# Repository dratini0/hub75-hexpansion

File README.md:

# HUB75 hexpansion

As of yet untested

Drives an LED wall panel by a single SPI peripheral.
A single 74HC595 drives the line select lines, this is inserted before the panel.
Then, the serial stream goes through the shift registers in the panel, and it is fed back into the input of the panel from the daisy chain output.
This means that a panel that normally needs a 6-way parallel drive can now be driven with just a single SPI line.
The OE pin is broken out to the high speed IO for a good measure.

The order of the chain is as follows:
1. Shift register
2. R1
3. G1
4. B1
5. R2
6. G2
7. B2

## Acknowledgements

Uses the [hexpansion template from EMF](https://github.com/emfcamp/badge-2024-hardware/tree/main/hexpansion)

I have taken the idea of chaining an LED wall panel with itself from some Youtube video that I have seen years and years ago, and I can no longer locate.

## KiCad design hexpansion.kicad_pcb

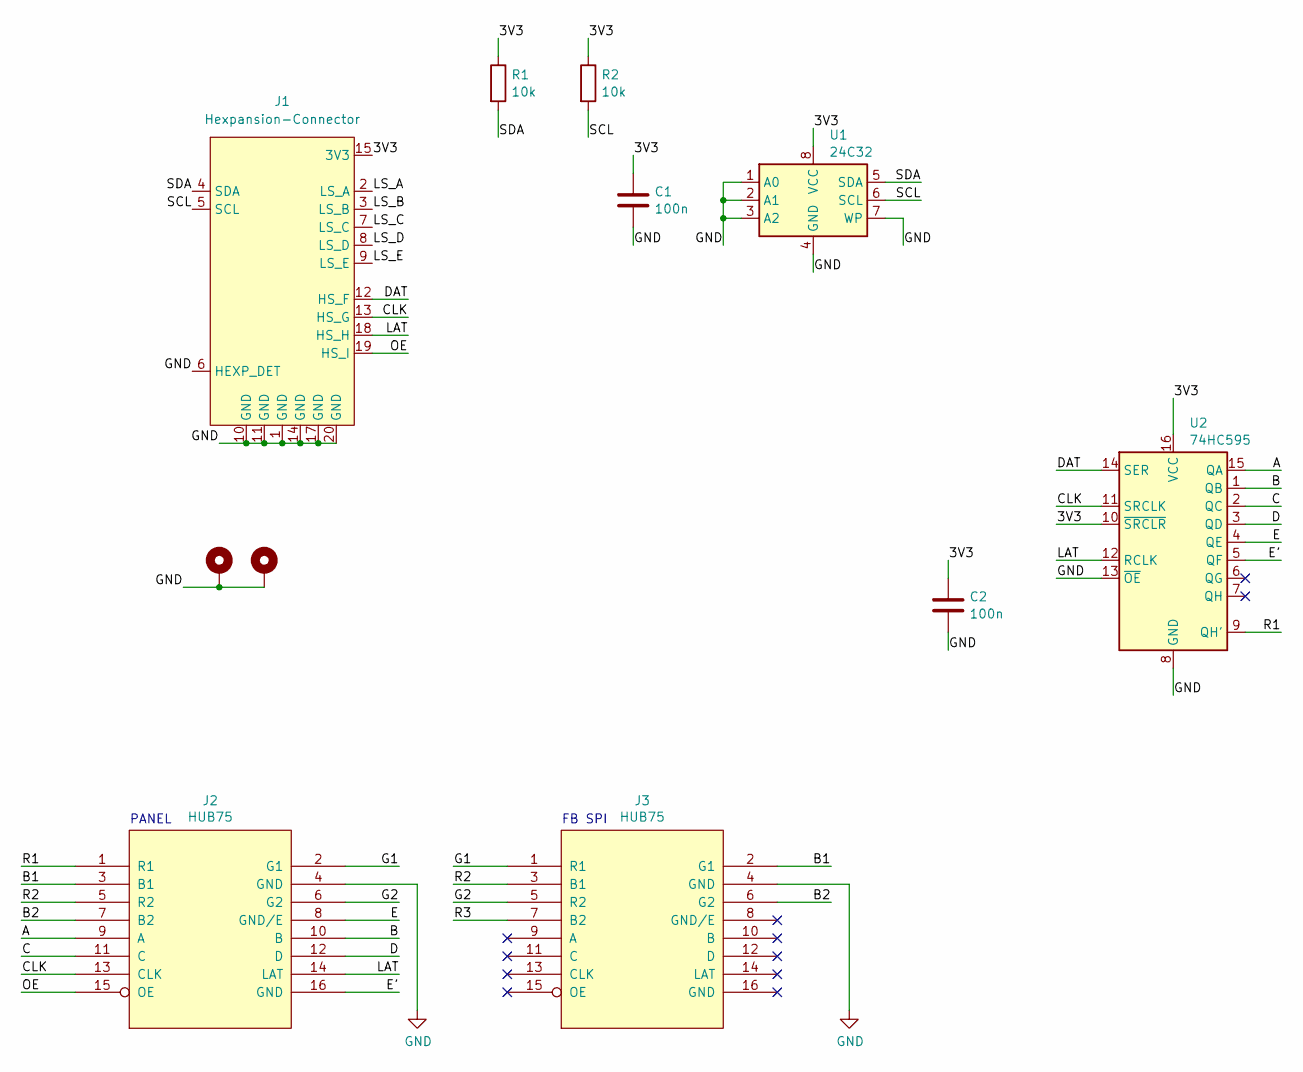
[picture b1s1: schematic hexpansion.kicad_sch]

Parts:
C1, C2: 100n; C_0805_2012Metric_Pad1.18x1.45mm_HandSolder
H1, H2: MountingHole_Pad; MountingHole_2.2mm_M2_Pad_Via
J1: Hexpansion-Connector; hexpansion-edge-connector
J2, J3: HUB75; IDC-Header_2x08_P2.54mm_Vertical
R1, R2: 10k; R_0805_2012Metric_Pad1.20x1.40mm_HandSolder
U1: 24C32; SOIC-8_3.9x4.9mm_P1.27mm
U2: 74HC595; SOIC-16_3.9x9.9mm_P1.27mm

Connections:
/3V3: C1.1, C2.1, J1.15 (3V3), J1.16 (3V3), R1.1, R2.1, U1.8 (VCC), U2.10 (~SRCLR), U2.16 (VCC)
/A: J2.9 (A), U2.15 (QA)
/B: J2.10 (B), U2.1 (QB)
/B1: J2.3 (B1), J3.2 (G1)
/B2: J2.7 (B2), J3.6 (G2)
/C: J2.11 (C), U2.2 (QC)
/CLK: J1.13 (HS_G), J2.13 (CLK), U2.11 (SRCLK)
/D: J2.12 (D), U2.3 (QD)
/DAT: J1.12 (HS_F), U2.14 (SER)
/E: J2.8 (GND/E), U2.4 (QE)
/E': J2.16 (GND), U2.5 (QF)
/G1: J2.2 (G1), J3.1 (R1)
/G2: J2.6 (G2), J3.5 (R2)
/LAT: J1.18 (HS_H), J2.14 (LAT), U2.12 (RCLK)
/LS_A: J1.2 (LS_A)
/LS_B: J1.3 (LS_B)
/LS_C: J1.7 (LS_C)
/LS_D: J1.8 (LS_D)
/LS_E: J1.9 (LS_E)
/OE: J1.19 (HS_I), J2.15 (OE)
/R1: J2.1 (R1), U2.9 (QH')
/R2: J2.5 (R2), J3.3 (B1)
/R3: J3.7 (B2)
/SCL: J1.5 (SCL), R2.2, U1.6 (SCL)
/SDA: J1.4 (SDA), R1.2, U1.5 (SDA)
GND: C1.2, C2.2, H1.1, H2.1, J1.1 (GND), J1.6 (HEXP_DET), J1.10 (GND), J1.11 (GND), J1.14 (GND), J1.17 (GND), J1.20 (GND), J2.4 (GND), J3.4 (GND), U1.1 (A0), U1.2 (A1), U1.3 (A2), U1.4 (GND), U1.7 (WP), U2.8 (GND), U2.13 (~OE)

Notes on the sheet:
PANEL
FB SPI

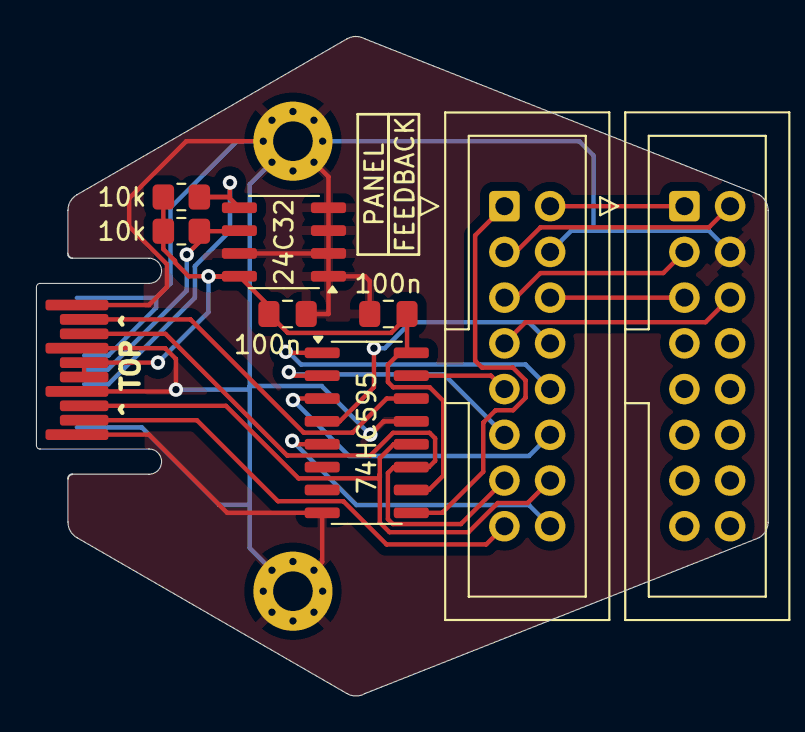
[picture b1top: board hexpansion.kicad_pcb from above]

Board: 2 copper layers, 40.6 x 36.6 mm, 11 parts (0 on the bottom side), 20 nets.

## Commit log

2024-05-28 Initial check in
